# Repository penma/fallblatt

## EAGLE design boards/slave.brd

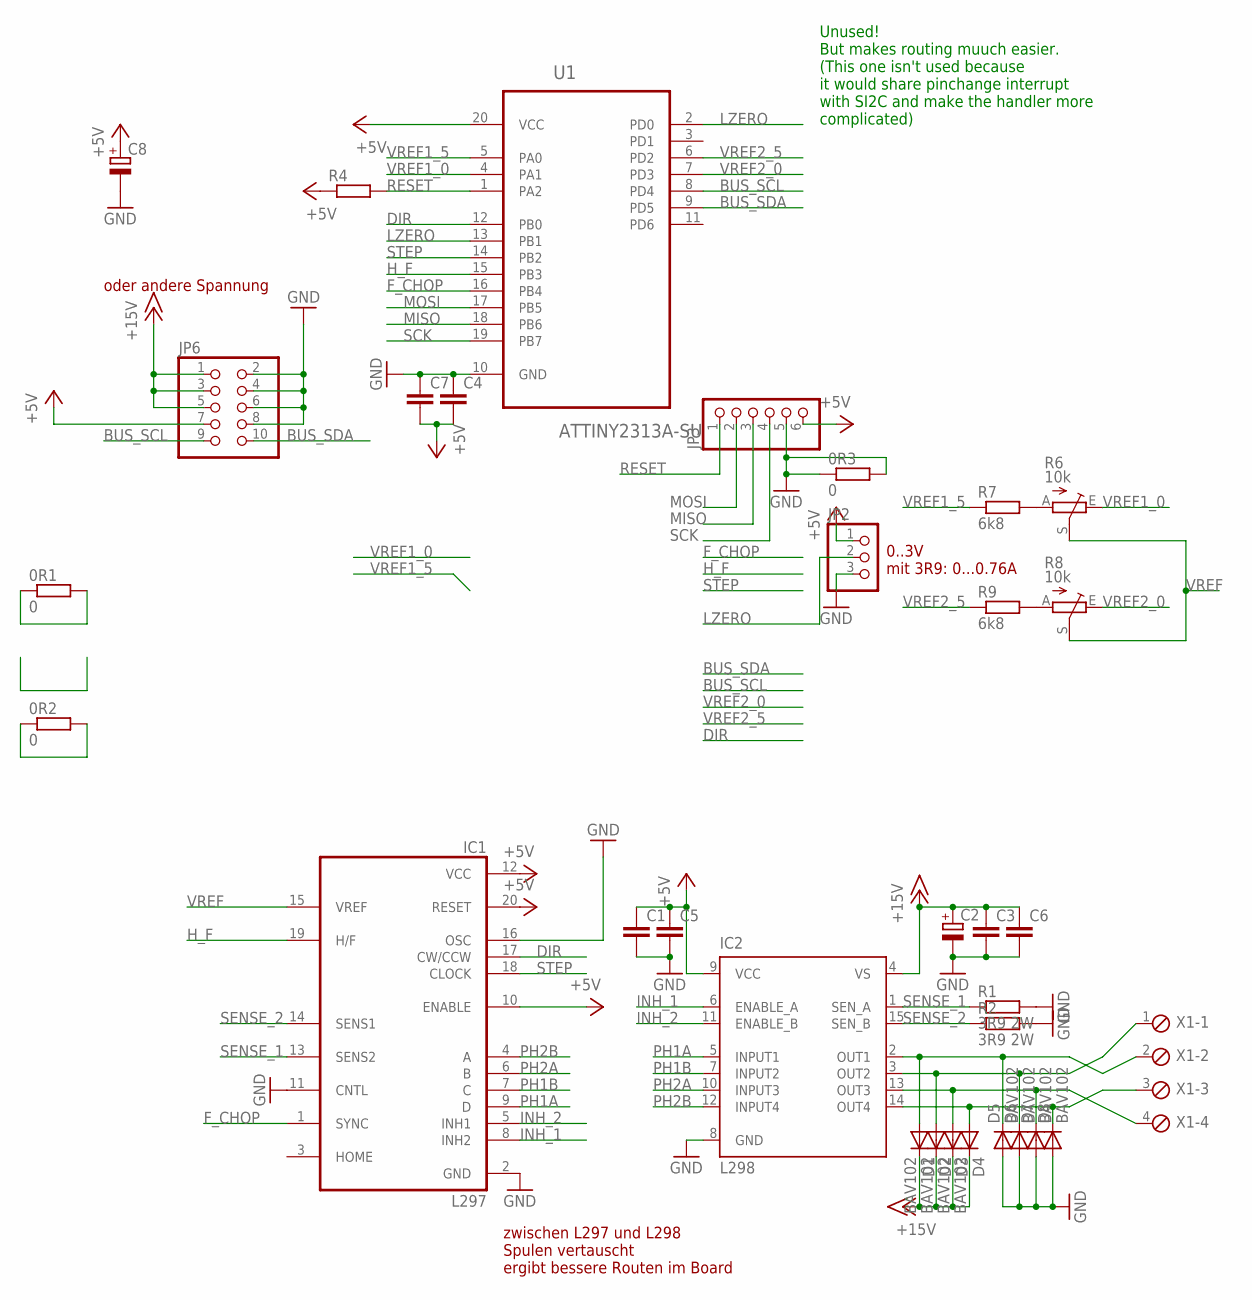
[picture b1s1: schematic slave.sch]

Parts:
0R1, 0R2, 0R3: 0; R1206
C1, C3, C4, C5, C6, C7: C-EUC0805; C0805
C2, C8: CPOL-EUE2.5-7; E2,5-7
D1, D2, D3, D4, D5, D6, D7, D8: BAV102; MINIMELF
IC1: L297; DIL20
IC2: L298; MULTIWATT-15
JP2: PINHD-1X3; 1X03
JP3: PINHD-1X6; 1X06
JP6: PINHD-2X5; 2X05
R1, R2: 3R9 2W; 0414/15
R4: R-EU_R1206; R1206
R6, R8: 10k; PT-10
R7, R9: 6k8; R1206
U1: ATTINY2313A-SU; SOIC127P1032X265-20N
X1: MPT4; 4POL254

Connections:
+5V: 0R1.1, 0R1.2, C1.1, C4.2, C5.1, C7.2, C8.+, IC1.10 (ENABLE), IC1.12 (VCC), IC1.20 (RESET), IC2.9 (VCC), JP2.1, JP3.6, JP6.7, R4.1, U1.20 (VCC)
+15V: C2.+, C3.1, C6.1, D1.C, D2.C, D3.C, D4.C, IC2.4 (VS), JP6.1, JP6.3, JP6.5
BUS_SCL: JP6.9, U1.8 (PD4)
BUS_SDA: JP6.10, U1.9 (PD5)
DIR: IC1.17 (CW/CCW), U1.12 (PB0)
F_CHOP: IC1.1 (SYNC), U1.16 (PB4)
GND: 0R3.1, 0R3.2, C1.2, C2.-, C3.2, C4.1, C5.2, C6.2, C7.1, C8.-, D5.A, D6.A, D7.A, D8.A, IC1.2 (GND), IC1.11 (CNTL), IC1.16 (OSC), IC2.8 (GND), JP2.3, JP3.5, JP6.2, JP6.4, JP6.6, JP6.8, R1.2, R2.2, U1.10 (GND)
H_F: IC1.19 (H/F), U1.15 (PB3)
INH_1: IC1.8 (INH2), IC2.6 (ENABLE_A)
INH_2: IC1.5 (INH1), IC2.11 (ENABLE_B)
LZERO: JP2.2, U1.2 (PD0), U1.13 (PB1)
MISO: JP3.3, U1.18 (PB6)
MOSI: JP3.2, U1.17 (PB5)
unnamed: R6.A, R7.2
unnamed: R8.A, R9.2
unnamed: D1.A, D5.C, IC2.2 (OUT1), X1.2
unnamed: D2.A, D6.C, IC2.3 (OUT2), X1.1
unnamed: D3.A, D7.C, IC2.13 (OUT3), X1.4
unnamed: D4.A, D8.C, IC2.14 (OUT4), X1.3
PH1A: IC1.9 (D), IC2.5 (INPUT1)
PH1B: IC1.7 (C), IC2.7 (INPUT2)
PH2A: IC1.6 (B), IC2.10 (INPUT3)
PH2B: IC1.4 (A), IC2.12 (INPUT4)
RESET: JP3.1, R4.2, U1.1 (PA2)
SCK: JP3.4, U1.19 (PB7)
SENSE_1: IC1.13 (SENS2), IC2.1 (SEN_A), R1.1
SENSE_2: IC1.14 (SENS1), IC2.15 (SEN_B), R2.1
STEP: IC1.18 (CLOCK), U1.14 (PB2)
VREF: 0R2.1, 0R2.2, IC1.15 (VREF), R6.S, R8.S
VREF1_0: R6.E, U1.4 (PA1)
VREF1_5: R7.1, U1.5 (PA0)
VREF2_0: R8.E, U1.7 (PD3)
VREF2_5: R9.1, U1.6 (PD2)

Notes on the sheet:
0..3V mit 3R9: 0...0.76A
oder andere Spannung
zwischen L297 und L298 Spulen vertauscht ergibt bessere Routen im Board
Unused! But makes routing muuch easier. (This one isn't used because it would share pinchange interrupt with SI2C and make the handler more complicated)

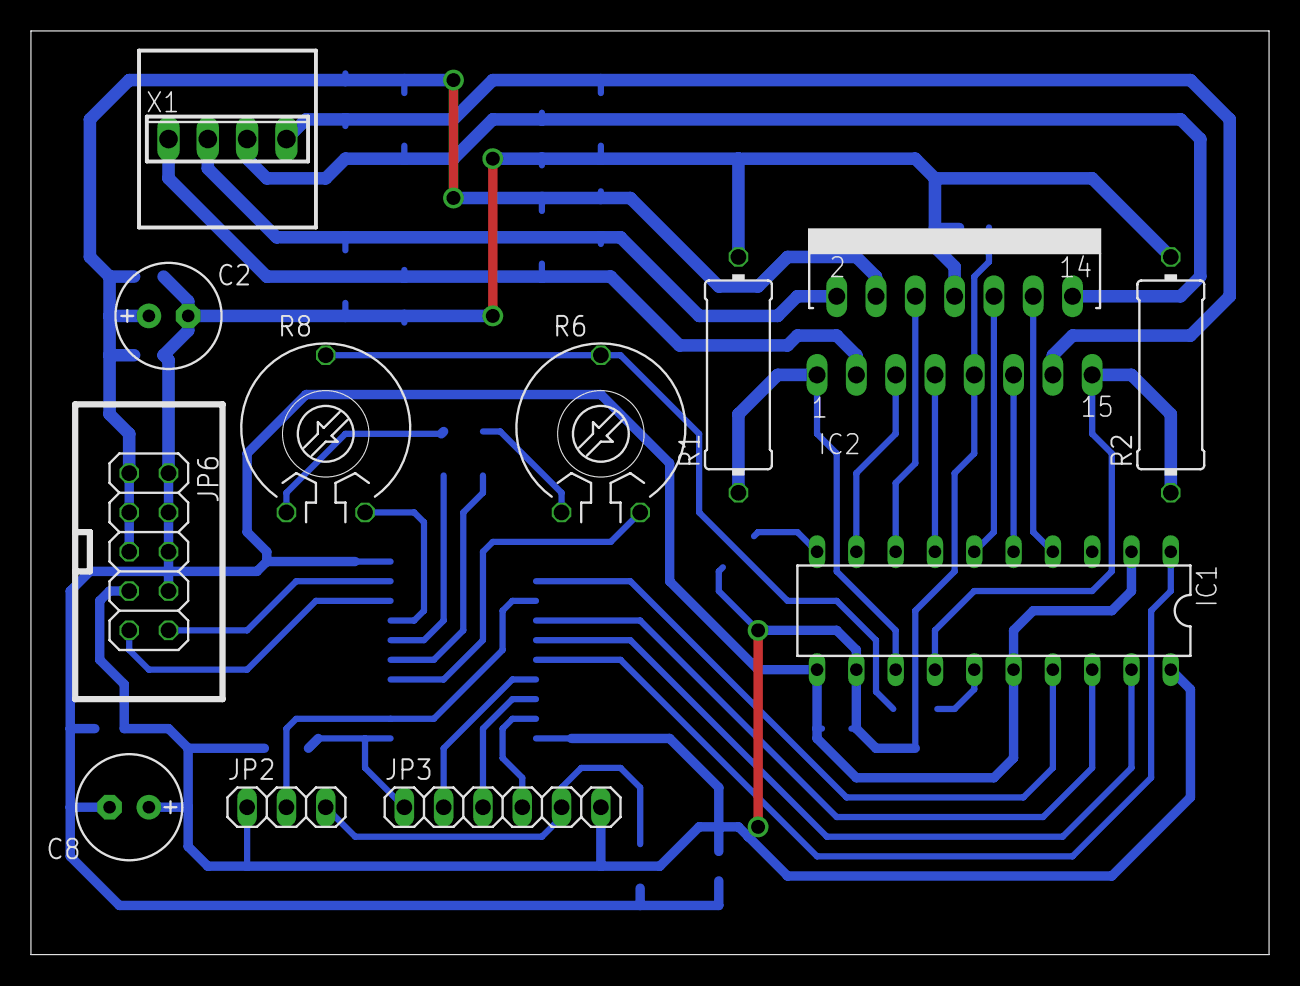
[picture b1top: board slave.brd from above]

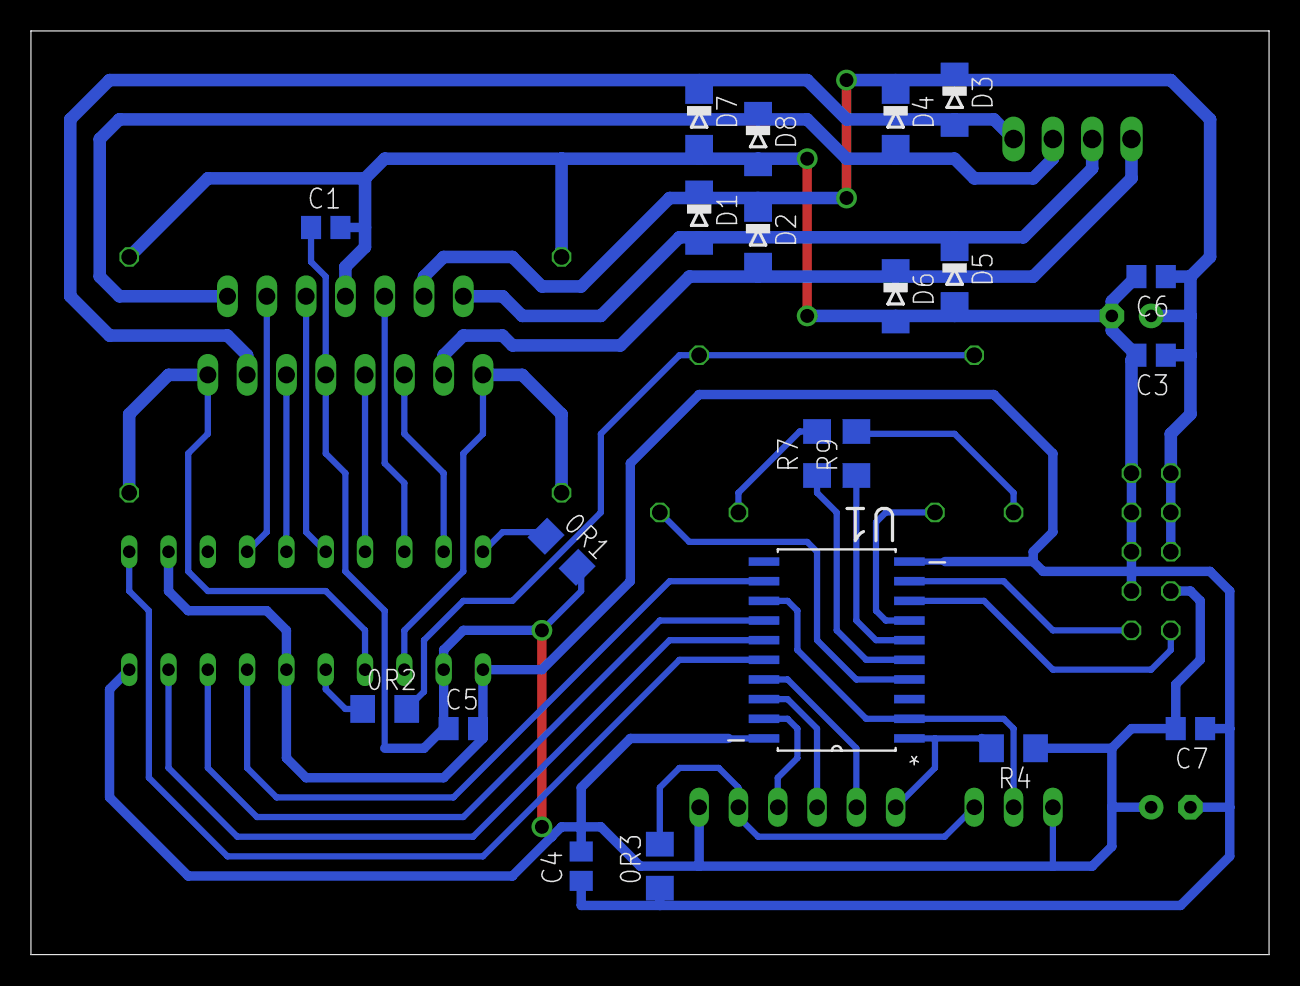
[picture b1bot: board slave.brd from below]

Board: 2 copper layers, 80.0 x 59.7 mm, 33 parts (21 on the bottom side), 33 nets.

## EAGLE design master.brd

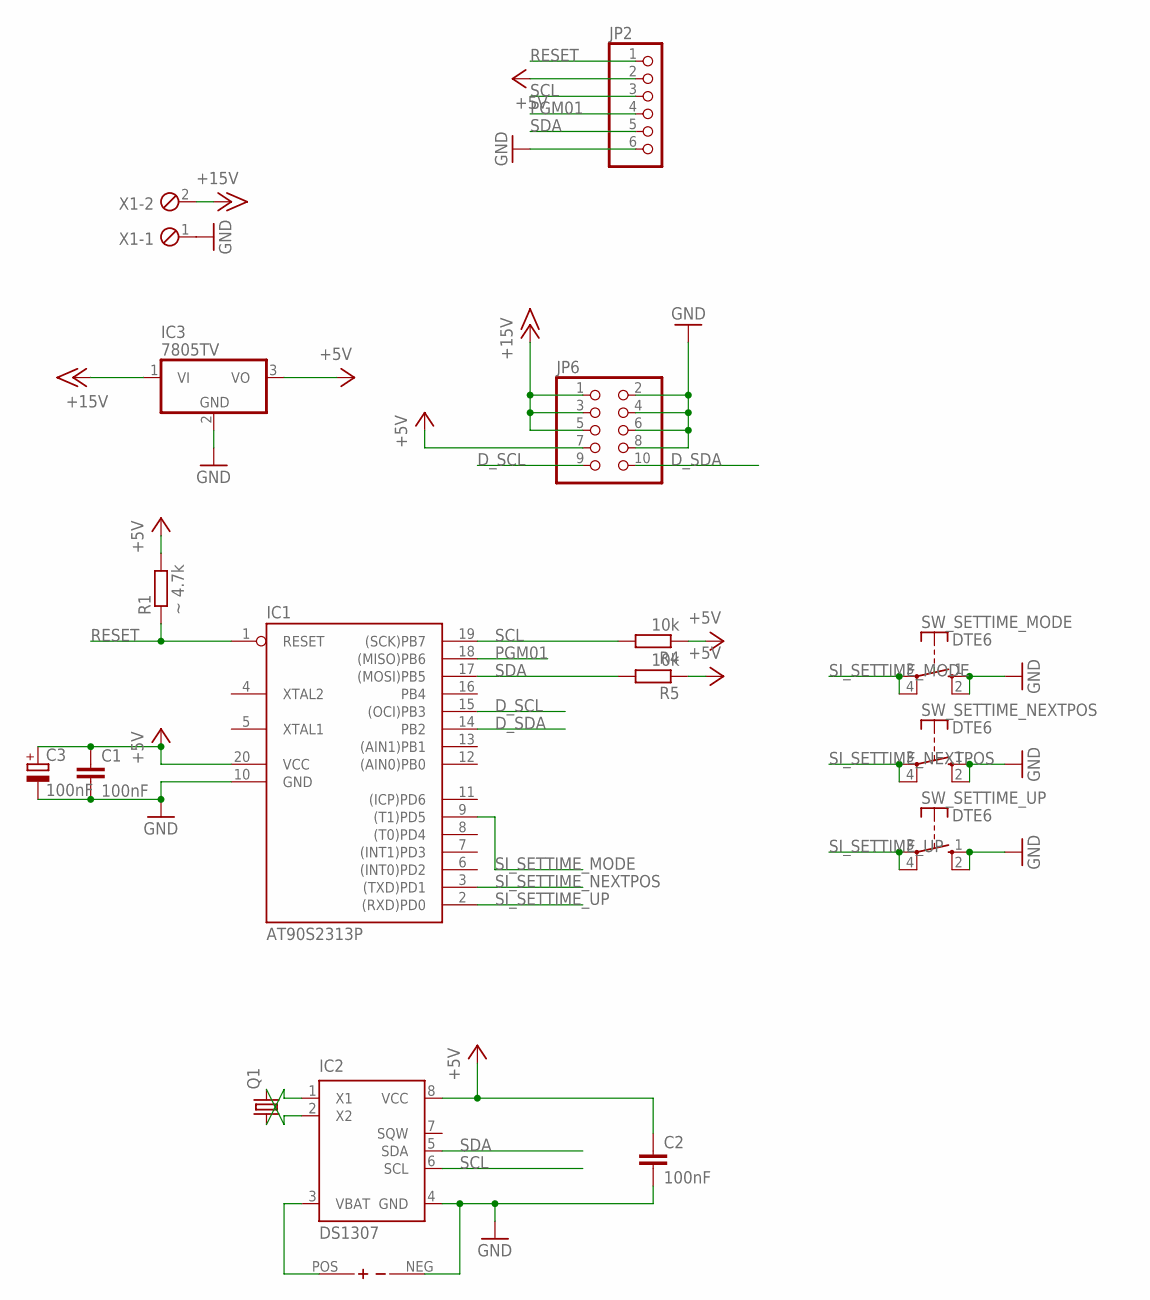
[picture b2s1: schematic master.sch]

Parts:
C1, C2: 100nF; C0805
C3: 100nF; E2,5-7
IC1: AT90S2313P; DIL20
IC2: DS1307; DIP-8
IC3: 7805TV; TO220V
JP2: PINHD-1X6; 1X06
JP6: PINHD-2X5; 2X05
Q1: CRYSTALQ-SMD-1MM; Q-SMD-1MM
R1: ~ 4.7k; 0207/10
R4, R5: 10k; 0207/10
SW_SETTIME_MODE: DTE6
SW_SETTIME_NEXTPOS: DTE6
SW_SETTIME_UP: DTE6
U$1: BATT
X1: MPT2; 2POL254

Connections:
+5V: C1.1, C2.1, C3.+, IC1.20 (VCC), IC2.8 (VCC), IC3.3 (VO), JP2.2, JP6.7, R1.2, R4.1, R5.1
+15V: IC3.1 (VI), JP6.1, JP6.3, JP6.5, X1.2
D_SCL: IC1.15 ((OCI)PB3), JP6.9
D_SDA: IC1.14 (PB2), JP6.10
GND: C1.2, C2.2, C3.-, IC1.10 (GND), IC2.4 (GND), IC3.2 (GND), JP2.6, JP6.2, JP6.4, JP6.6, JP6.8, SW_SETTIME_MODE.1 (S), SW_SETTIME_MODE.2 (S), SW_SETTIME_NEXTPOS.1 (S), SW_SETTIME_NEXTPOS.2 (S), SW_SETTIME_UP.1 (S), SW_SETTIME_UP.2 (S), U$1.NEG (V-), X1.1
unnamed: IC2.1 (X1), Q1.1
unnamed: IC2.2 (X2), Q1.2
PGM01: IC1.18 ((MISO)PB6), JP2.4
RESET: IC1.1 (RESET), JP2.1, R1.1
SCL: IC1.19 ((SCK)PB7), IC2.6 (SCL), JP2.3, R4.2
SDA: IC1.17 ((MOSI)PB5), IC2.5 (SDA), JP2.5, R5.2
SI_SETTIME_MODE: IC1.9 ((T1)PD5), SW_SETTIME_MODE.3, SW_SETTIME_MODE.4
SI_SETTIME_NEXTPOS: IC1.3 ((TXD)PD1), SW_SETTIME_NEXTPOS.3, SW_SETTIME_NEXTPOS.4
SI_SETTIME_UP: IC1.2 ((RXD)PD0), SW_SETTIME_UP.3, SW_SETTIME_UP.4
VBAT: IC2.3 (VBAT), U$1.POS (V+)

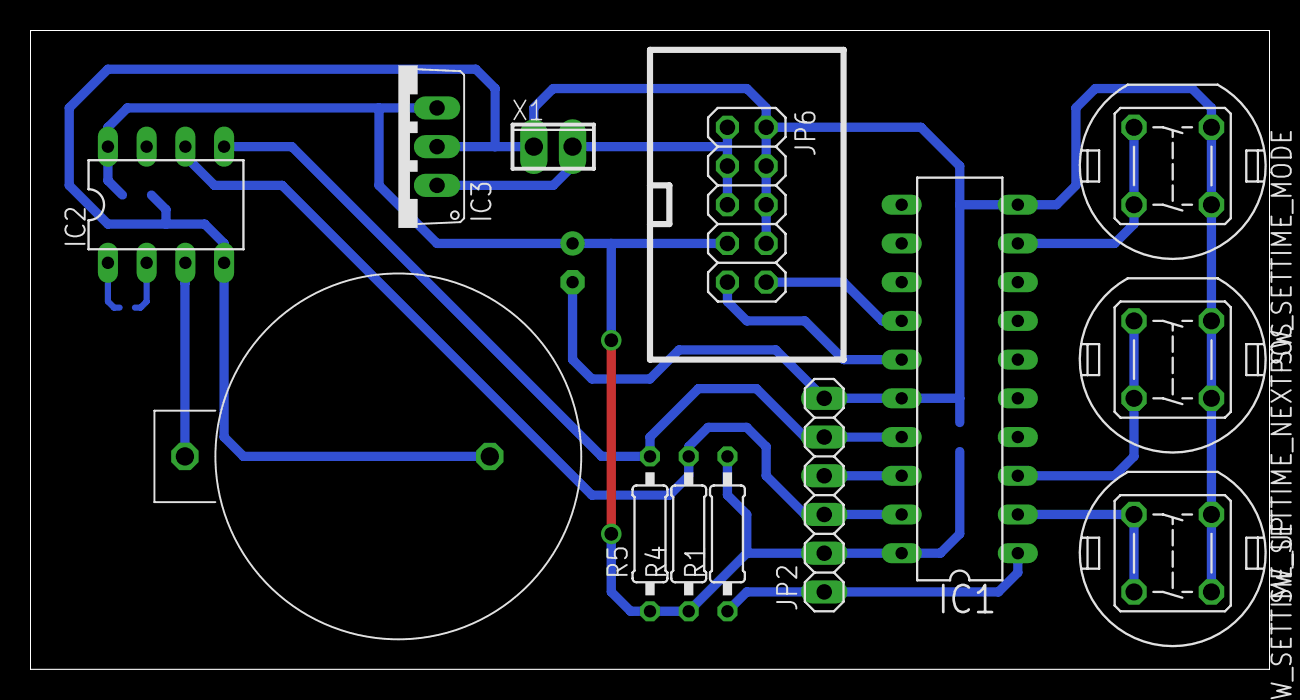
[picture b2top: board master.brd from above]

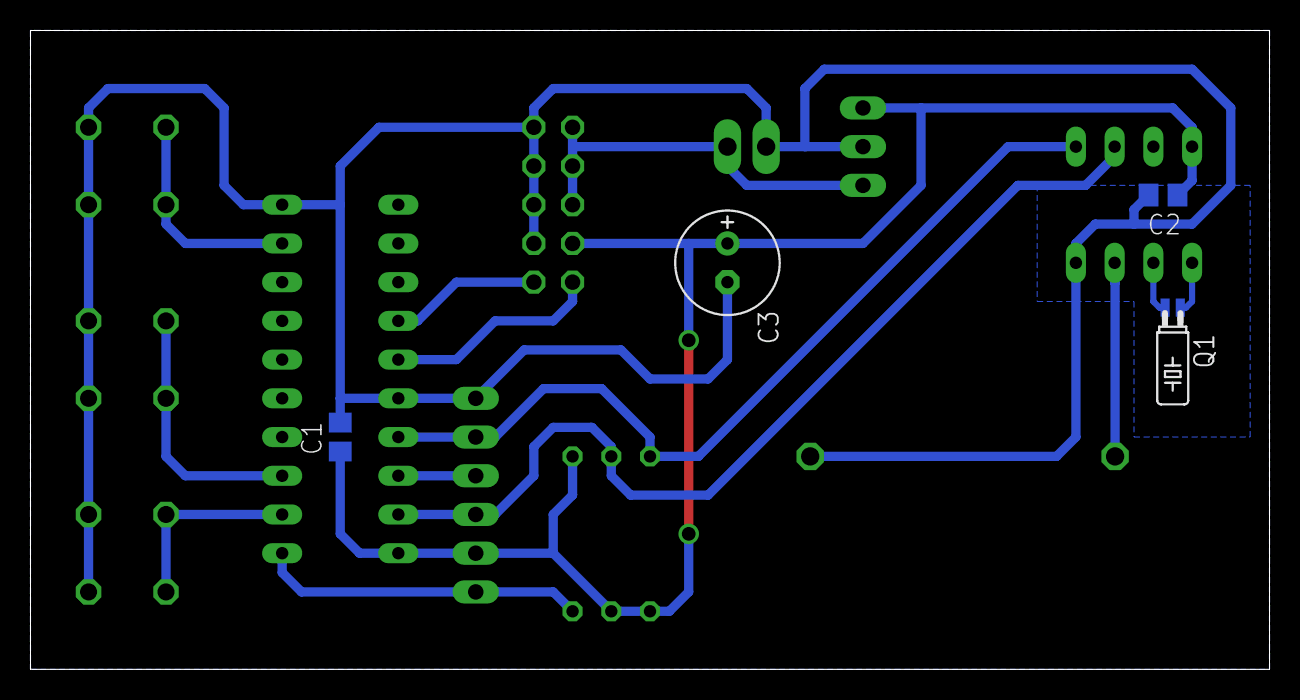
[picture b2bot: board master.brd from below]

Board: 2 copper layers, 81.3 x 41.9 mm, 17 parts (4 on the bottom side), 15 nets.

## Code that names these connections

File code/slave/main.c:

#include <avr/io.h>
#include <avr/interrupt.h>
#include <avr/wdt.h>
#include <util/delay.h>
#include <stdlib.h>
#include "si2c_slave.h"
#include "debug.h"

#define RECALIB PD1

volatile uint16_t current_pos;
volatile uint16_t target_pos;
volatile uint16_t steps_until_done;

/* configuration */

uint8_t conf_steps_per_num;
uint8_t conf_numbers;
uint16_t conf_steps_total;
uint8_t conf_offset;
uint8_t conf_address;

extern uint8_t __eerd_byte_tn2313(uint8_t *);
static uint8_t eerd(uint8_t addr) {
	/* avr-libc in the version I used did not properly declare eeprom read
	 * functions for the tiny2313A. therefore, this hack
	 */
	return __eerd_byte_tn2313((uint8_t*) addr);
}

static void config_read() {
	conf_steps_per_num = eerd(1);
	conf_numbers = eerd(2);
	conf_offset = eerd(3);
	conf_address = eerd(4);

	conf_steps_total = conf_steps_per_num * conf_numbers;
}





/* light sensor for finding start position */

#define LZERO PB1

static void lightsensor_init() {
	DDRB &= ~(1 << LZERO); /* configure pin as input */
	PORTB |= (1 << LZERO); /* with pull-up enabled */

	GIMSK |= (1 << 5 /* PCIE0 */);
	PCMSK /* 0 */ |= (1 << PCINT1);
}

static int lightsensor_is_blocked() {
	return PINB & (1 << LZERO);
}

ISR (PCINT_B_vect) {
	/* PB1! */
	if (!lightsensor_is_blocked() && current_pos > conf_steps_per_num) {
		current_pos = 0;
	}
}


/* stepper motor control */

#define VREF1_0 PA1
#define VREF1_5 PA0
#define VREF2_0 PD3
#define VREF2_5 PD2
#define STEP PB2

static void motor_current_active() {
	/* disable vref2 */
	DDRD &= ~( (1 << VREF2_0) | (1 << VREF2_5) );
	PORTD &= ~(1 << VREF2_5);

	/* enable vref1 */
	DDRA |= (1 << VREF1_0) | (1 << VREF1_5);
	PORTA |= (1 << VREF1_5);
}

static void motor_current_idle() {
	/* disable vref1 */
	DDRA &= ~( (1 << VREF1_0) | (1 << VREF1_5) );
	PORTA &= ~(1 << VREF1_5);

	/* enable vref2 */
	DDRD |= (1 << VREF2_0) | (1 << VREF2_5);
	PORTD |= (1 << VREF2_5);
}

static void motor_step() {
	PORTB |= (1 << STEP);
	_delay_us(10);
	PORTB &= ~(1 << STEP);
	_delay_us(10);
}

#define DIR PB0
#define FCHOP PB4
#define H_F PB3

static void motor_init() {
	DDRB |= (1 << STEP) | (1 << H_F) | (1 << FCHOP) | (1 << DIR);
	PORTB |= (1 << DIR);

	/* Configure Timer1 to output about 30 kHz on OC1B / PB4 / pin 16.
	 * L297 uses this signal to limit motor current
	 */
	TCCR1A = (1 << COM1B0);
	TCCR1B = (1 << WGM12) | (1 << CS11);
	TCCR1C = (1 << FOC1B);
	OCR1A = 0x10;
	#if F_CPU != 8000000
	#warning Hardcoded value for OCR1A is only correct for 8 MHz clock, please check
	#endif
}

static void find_start_position() {
	motor_current_active();

	/* Move until we find the hole in the wheel.
	 * The hole identifies a position between digits 9 and 0.
	 */
	while (lightsensor_is_blocked()) {
		motor_step();
		_delay_ms(9);
		/* FIXME: will position incorrectly if stopped over marking at powerup.
		 * maybe force it to get blocked first, then unblocked?
		 */
	}

	/* Move by configured offset, so we display number zero
	 * (the mark on the wheel is between 9 and 0)
	 */
	for (int i = 0; i < conf_offset; i++) {
		motor_step();
		_delay_ms(13);
	}

	/* Record our current position */
	current_pos = conf_offset;
	target_pos = conf_offset;
	steps_until_done = 0;

	motor_current_idle();

	_delay_ms(100);
}


void update_target(uint16_t new_target) {
	target_pos = new_target;

	steps_until_done = conf_steps_total + target_pos - current_pos;
	if (steps_until_done >= conf_steps_total) {
		steps_until_done -= conf_steps_total;
	}
}

void si2cs_received(uint8_t *buf, uint8_t len) {
	if (len != 3) return;

	if (buf[0] == 0xba) {
		if (buf[1] == conf_address) {
			uint16_t new_target = (buf[2] * conf_steps_per_num + conf_offset);
			if (new_target > conf_steps_total) {
				new_target -= conf_steps_total;
			}
			update_target(new_target);
		}
	}
}


void init_disable_watchdog() __attribute__((naked)) __attribute__((section(".init3")));
void init_disable_watchdog() {
	MCUSR = 0;
	wdt_disable();
}

int main (void) {
	debug_init();

	config_read();

	motor_init();
	lightsensor_init();

	find_start_position();

	debug_fstr("done");
	lcd_setcursor(2,2);
	debug_fstr("durr ");
	debug_hex8(conf_address);

	/* now listen on the bus and wait for data */
	si2cs_init();
	sei();

	/* we're done with setup. activate watchdog */
	wdt_enable(WDTO_4S);

	while (1) {
		/* moving to a new position */

		motor_current_active();

		uint16_t steps_since_start = 0;

		while (current_pos != target_pos) {
			/* do one step */
			motor_step();

			/* update current position.
			 * overflow of the current position is handled by the
			 * light sensor interrupt
			 */
			current_pos++;

			/* acceleration */
			if (steps_since_start > 20 && steps_until_done > 20) {
				_delay_ms(3);
			} else if (steps_since_start > 10 && steps_until_done > 10) {
				_delay_ms(6);
			} else if (steps_since_start > 5 && steps_until_done > 5) {
				_delay_ms(9);
			} else {
				_delay_ms(10);
			}
			steps_since_start++;
			steps_until_done--;

			wdt_reset();
		}

		/* holding the current position */

		motor_current_idle();

		while (current_pos == target_pos) {
			_delay_ms(20);

			wdt_reset();
		}
	}
}

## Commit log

2013-11-27 initial
2013-11-29 Schnecke vorgerendert (spart Zeit!)
2013-11-30 Aufnahme für Motor + Kugellager
2013-12-01 Motoraufnahme optimiert
2013-12-03 Nupsi
2013-12-03 Motor Gegenstück 1mm flacher, kollidiert dann nicht mehr mit Schnecke
2013-12-04 Motoraufnahme: gefixt und in mehr Funktionen zerteilt
2013-12-04 Motoraufnahme: Schnecke nicht aus stl
2013-12-04 Mittelstift und Blaetterrad Demos umstrukturiert
2013-12-04 Mittelstift: muss nicht 100% hohl sein
2013-12-05 Mittelstift: Druckeinstellungen dazu
2013-12-05 RahmenVerbinder: neuer Verbinder für die Seitenteile
    (vormals mit Seitenteil verbunden)
2013-12-06 seitenteil etwas geupdated
2013-12-06 neues seitenteil
2013-12-06 Schnecke verlängert
2013-12-07 Seitenteil neu gebaut
2013-12-08 Seitenteil: Wandstärke runter
2013-12-08 Rahmenverbinder: mehr Parameter.
    (bisschen was fehlt noch)
2013-12-08 Rahmen: Nupsis weg und Löcher für durchgehende Achse rein
    Rahmen neigt dazu sich genau am Rad nach außen zu biegen. Mit Nupsis ist das
    ein Problem, auch wenn es mit langen Nupsis noch funktioniert. Suboptimal
    ist das trotzdem
    Lösung: Achse durchgehend und beidseitig verkleben.
2013-12-08 Mittelstift wieder durchgehend hohl
2013-12-12 Innenabstand verbreitert, mehr Zahnräder
2013-12-14 Lasercut template (25x50 cm)
2013-12-14 Radlager verkleinert
    Da wird eh nie ein Kugellager eingebaut und damit verbraucht es nur unnötig
    Platz im Rahmen. -> Kleiner machen
2013-12-14 Mehr Zahnräder!
2013-12-14 Schnecke+Rad modifiziert, Seitenteil angepasst
2013-12-15 Schnecke: neu gedruckt -> Daten.
2013-12-16 Blätterrad: Löcher verkleinert, Zahnrad verkleinert, durchgehendes Loch
2013-12-18 seitenteil updated
2014-01-02 random änderungen der letzten tage
2014-01-04 various fixes
    Lichtschranke Montage optimiert
    Lichtschranke Rad enger gemacht (weniger Wackeln)
    Seitenteil Achse nach hinten verschoben (sonst durchrutschen)
2014-01-06 Achse 5mm -> 4mm
2014-01-07 aufräumen
2014-01-07 bisschen weniger mischmasch
2014-01-07 Seitenteil: etwas mehr Lesbarkeit
2014-01-07 mehr aufräumen
2014-03-11 anscheinend letzte Version von v1
2014-03-16 lol, steppermount
2014-04-16 steppermount!
2014-06-07 Teile
2014-06-07 seitenteil etwas entmüllen
2014-06-07 Seitenwand mehr entmüllt
2014-06-07 mehr weniger Müll
2014-06-07 mehr ausmisten
2014-06-07 Motordummy ist nicht Teil des Objekts
2014-06-07 Mehr Eaglefiles!
2014-06-07 ...und verschoben
2014-06-07 Mehr Code
